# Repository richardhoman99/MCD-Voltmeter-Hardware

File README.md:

# MCD-Voltmeter-Hardware
The KiCad project for the MCD Voltmeter project.  
See "PCB Voltmeter Report.pdf"

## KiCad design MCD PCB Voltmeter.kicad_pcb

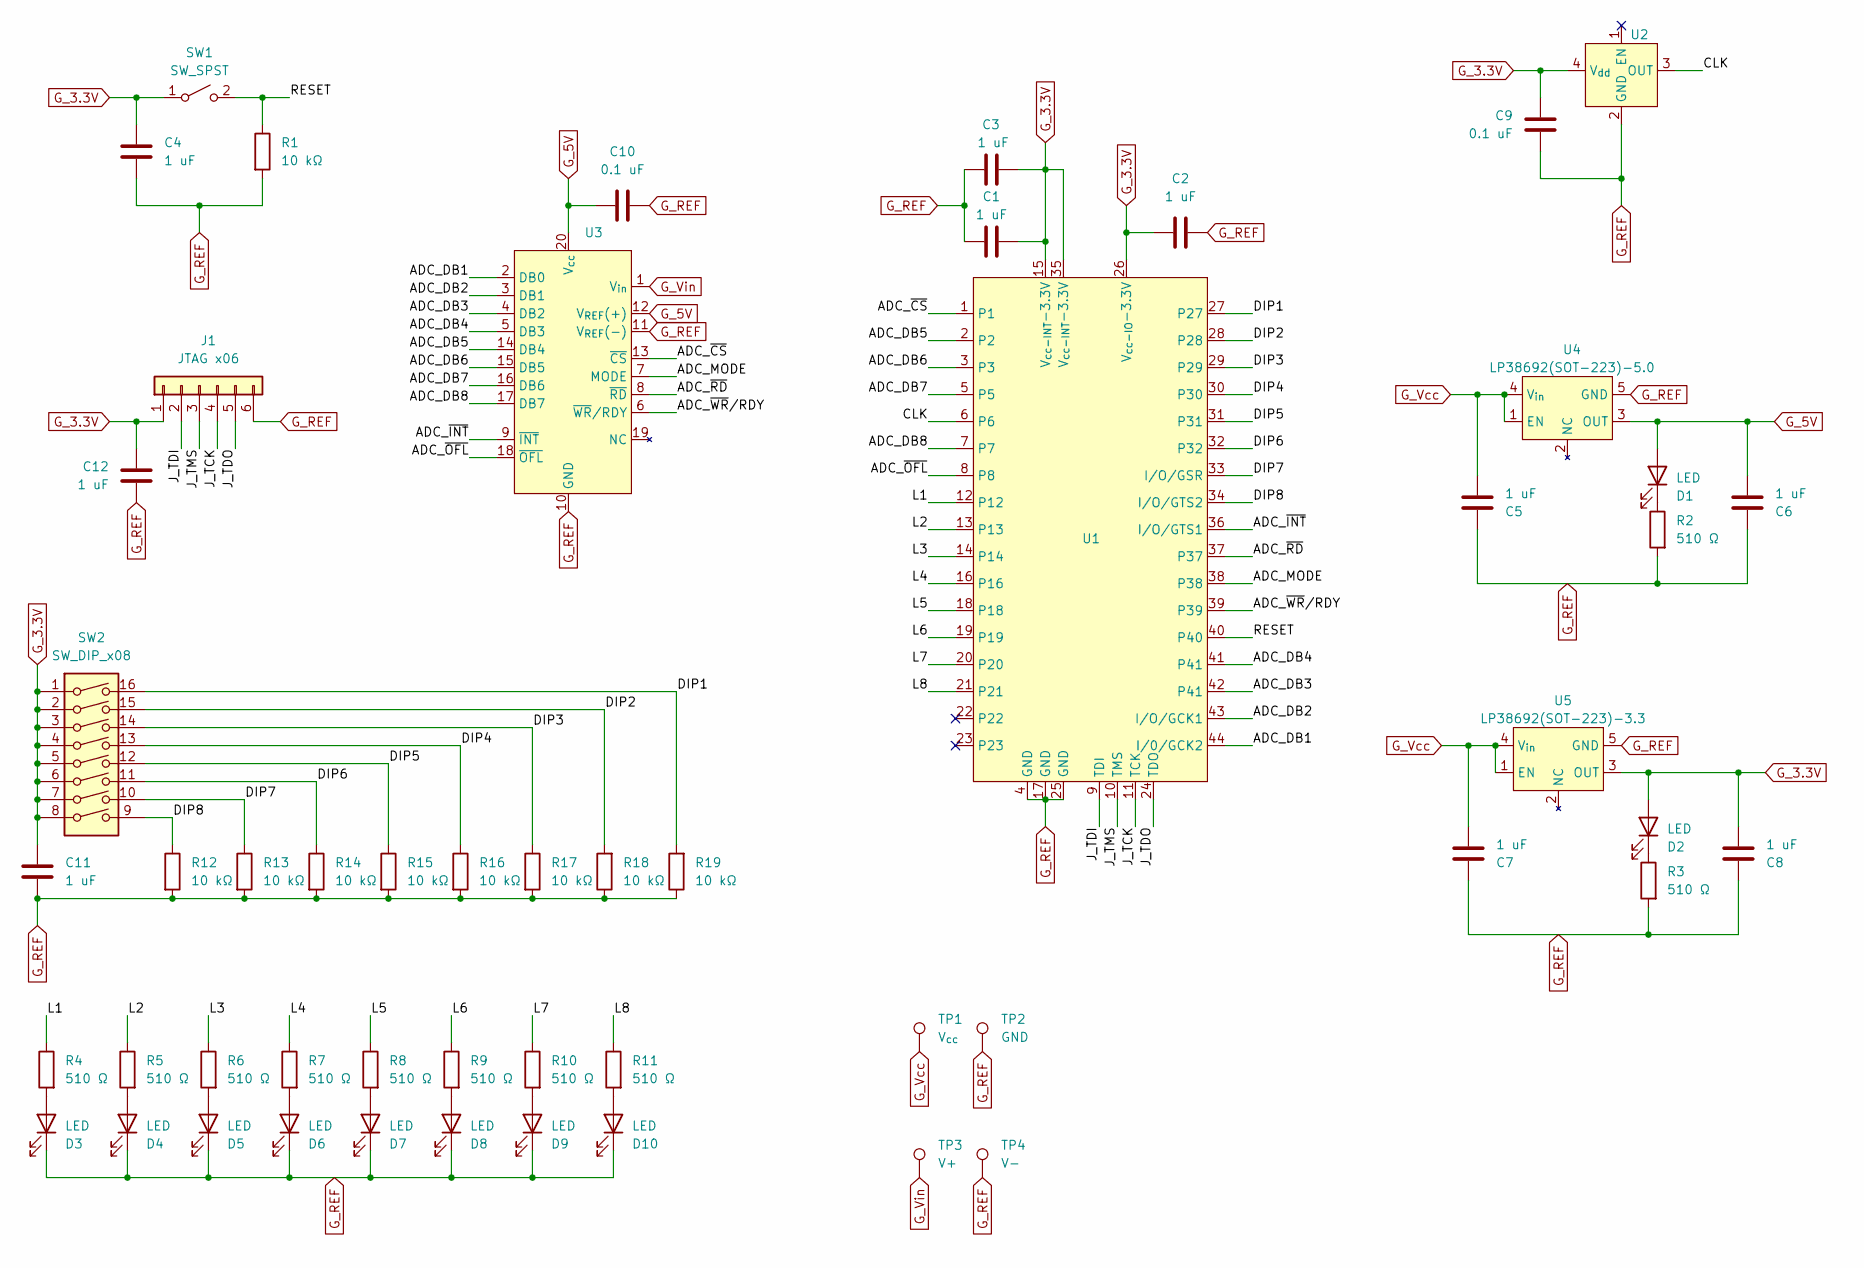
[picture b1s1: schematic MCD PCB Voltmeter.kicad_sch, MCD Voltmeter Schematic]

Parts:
C1, C2, C3, C4, C5, C6, C7, C8, C11, C12: 1 uF; C_0805_2012Metric
C9, C10: 0.1 uF; C_0805_2012Metric
D1, D2, D3, D4, D5, D6, D7, D8, D9, D10: LED; LED_0805_2012Metric
J1: JTAG x06; PinHeader_1x06_P2.54mm_Vertical
R1, R12, R13, R14, R15, R16, R17, R18, R19: 10 kΩ; C_0805_2012Metric
R2, R3, R4, R5, R6, R7, R8, R9, R10, R11: 510 Ω; C_0805_2012Metric
SW1: SW_SPST; SW_SPST_EVQQ2
SW2: SW_DIP_x08; SW_DIP_SPSTx08_Slide_6.7x21.88mm_W6.73mm_P2.54mm_LowProfile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
TP1: V_{cc}; TestPoint_Keystone_4952
TP2: GND; TestPoint_Keystone_4952
TP3: V+; TestPoint_Keystone_4952
TP4: V-; TestPoint_Keystone_4952
U1: VQFP-44_10x10mm_P0.8mm
U2: Crystal_SMD_5032-4Pin_5.0x3.2mm
U3: SOIC-20W_7.5x12.8mm_P1.27mm
U4: LP38692(SOT-223)-5.0; SOT-223-5
U5: LP38692(SOT-223)-3.3; SOT-223-5

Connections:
/ADC_DB1: U1.44 (I/0/GCK2), U3.2 (DB0)
/ADC_DB2: U1.43 (I/O/GCK1), U3.3 (DB1)
/ADC_DB3: U1.42 (P41), U3.4 (DB2)
/ADC_DB4: U1.41, U3.5 (DB3)
/ADC_DB5: U1.2, U3.14 (DB4)
/ADC_DB6: U1.3, U3.15 (DB5)
/ADC_DB7: U1.5, U3.16 (DB6)
/ADC_DB8: U1.7, U3.17 (DB7)
/ADC_MODE: U1.38, U3.7 (MODE)
/ADC_~CS: U1.1, U3.13 (~CS)
/ADC_~INT: U1.36 (I/O/GTS1), U3.9 (~INT)
/ADC_~OFL: U1.8, U3.18 (~OFL)
/ADC_~RD: U1.37, U3.8 (~RD)
/ADC_~WR/RDY: U1.39, U3.6 (~WR/RDY)
/CLK: U1.6, U2.3 (OUT)
/DIP1: R19.2, SW2.16, U1.27
/DIP2: R18.2, SW2.15, U1.28
/DIP3: R17.1, SW2.14, U1.29
/DIP4: R16.1, SW2.13, U1.30
/DIP5: R15.1, SW2.12, U1.31
/DIP6: R14.1, SW2.11, U1.32
/DIP7: R13.1, SW2.10, U1.33 (I/O/GSR)
/DIP8: R12.1, SW2.9, U1.34 (I/O/GTS2)
/J_TCK: J1.4, U1.11 (TCK)
/J_TDI: J1.2, U1.9 (TDI)
/J_TDO: J1.5, U1.24 (TDO)
/J_TMS: J1.3, U1.10 (TMS)
/L1: R4.1, U1.12
/L2: R5.1, U1.13
/L3: R6.1, U1.14
/L4: R7.1, U1.16
/L5: R8.1, U1.18
/L6: R9.1, U1.19
/L7: R10.1, U1.20
/L8: R11.1, U1.21
/RESET: R1.1, SW1.2 (B), U1.40
G_3.3V: C1.2, C2.1, C3.2, C4.1, C8.1, C9.1, C11.1, C12.1, D2.2 (A), J1.1, SW1.1 (A), SW2.1, SW2.2, SW2.3, SW2.4, SW2.5, SW2.6, SW2.7, SW2.8, U1.15 (V_{cc-INT}-3.3V), U1.26 (V_{cc-IO}-3.3V), U1.35 (V_{cc-INT}-3.3V), U2.4 (V_{dd}), U5.3 (OUT)
G_5V: C6.1, C10.1, D1.2 (A), U3.12 (V_{REF}(+)), U3.20 (V_{cc}), U4.3 (OUT)
G_REF: C1.1, C2.2, C3.1, C4.2, C5.2, C6.2, C7.2, C8.2, C9.2, C10.2, C11.2, C12.2, D3.1 (K), D4.1 (K), D5.1 (K), D6.1 (K), D7.1 (K), D8.1 (K), D9.1 (K), D10.1 (K), J1.6, R1.2, R2.2, R3.2, R12.2, R13.2, R14.2, R15.2, R16.2, R17.2, R18.1, R19.1, TP2.1, TP4.1, U1.4 (GND), U1.17 (GND), U1.25 (GND), U2.2 (GND), U3.10 (GND), U3.11 (V_{REF}(-)), U4.5 (GND), U5.5 (GND)
G_Vcc: C5.1, C7.1, TP1.1, U4.1 (EN), U4.4 (V_{in}), U5.1 (EN), U5.4 (V_{in})
G_Vin: TP3.1, U3.1 (V_{in})
unnamed: D1.1 (K), R2.1
unnamed: D2.1 (K), R3.1
unnamed: D3.2 (A), R4.2
unnamed: D4.2 (A), R5.2
unnamed: D5.2 (A), R6.2
unnamed: D6.2 (A), R7.2
unnamed: D7.2 (A), R8.2
unnamed: D8.2 (A), R9.2
unnamed: D9.2 (A), R10.2
unnamed: D10.2 (A), R11.2

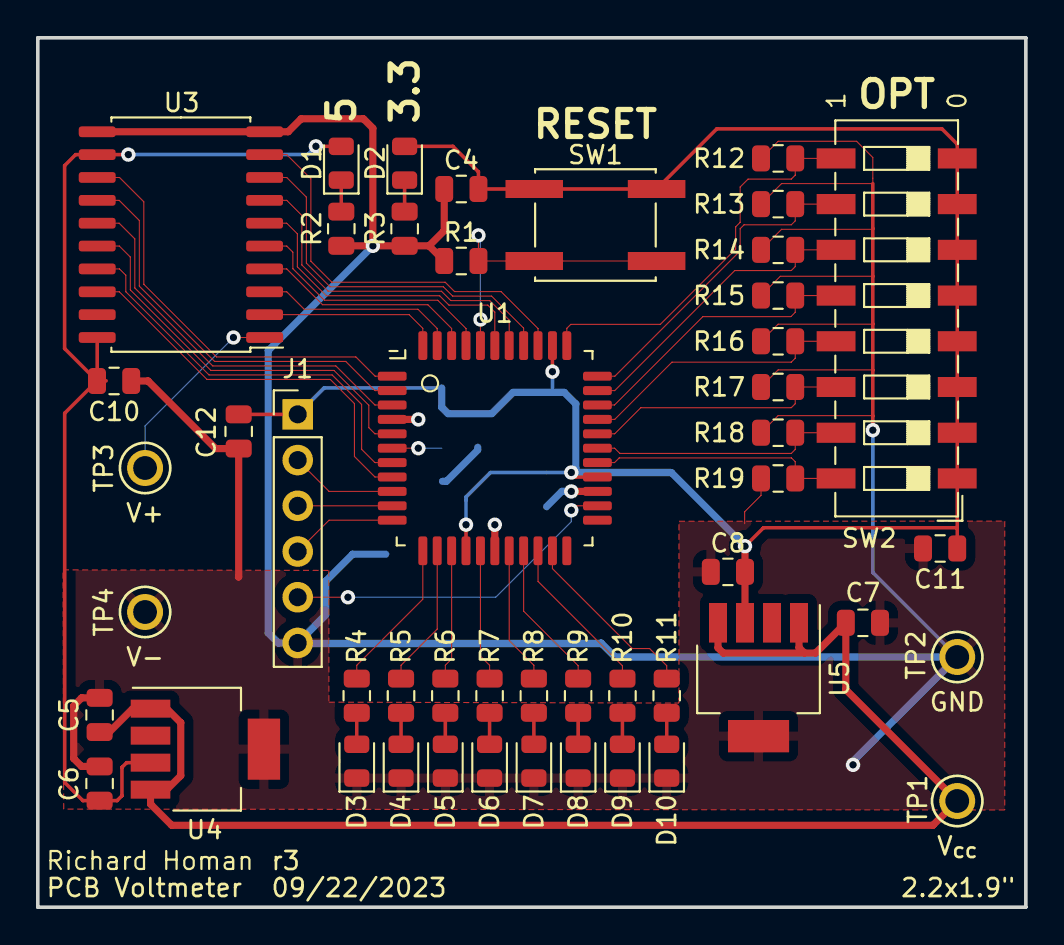
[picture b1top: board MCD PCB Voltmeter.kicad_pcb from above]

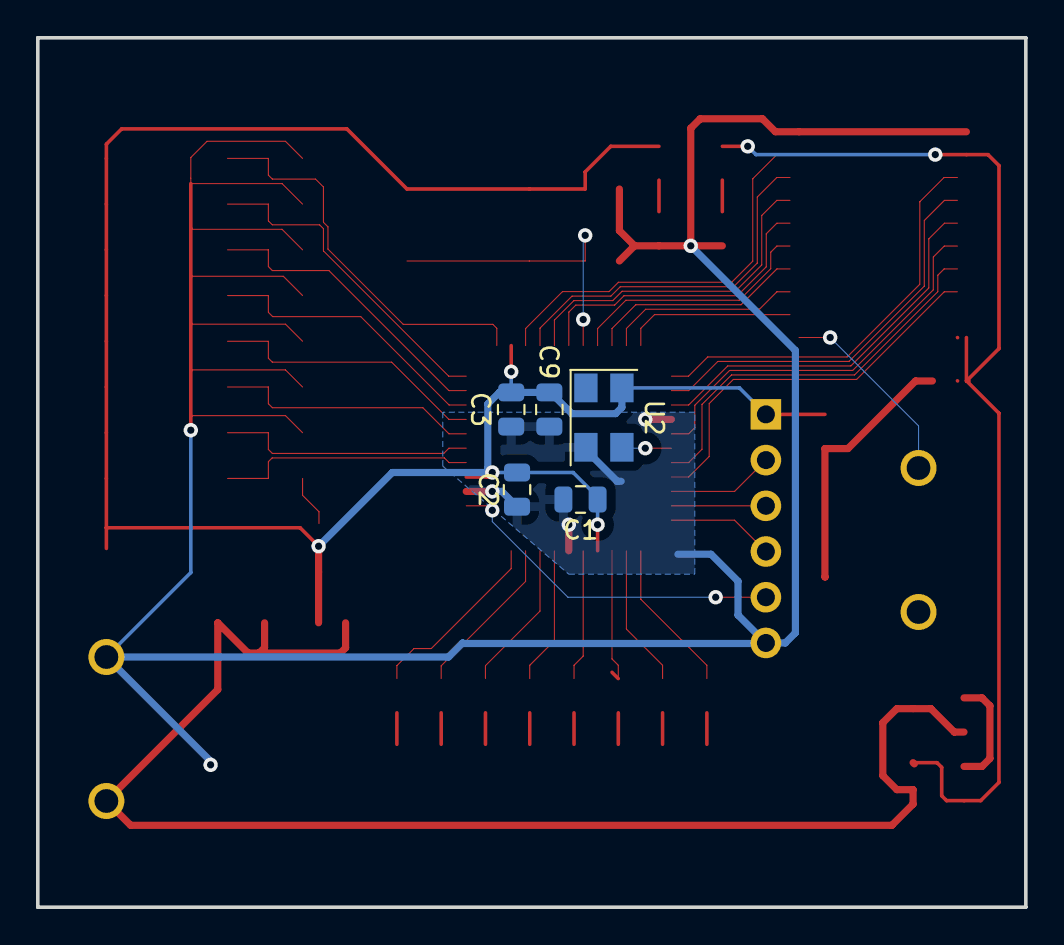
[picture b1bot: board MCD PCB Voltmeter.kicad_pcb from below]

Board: 2 copper layers, 54.9 x 48.3 mm, 53 parts (5 on the bottom side), 51 nets.

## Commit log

2023-11-03 Initial commit
    Copy items to Github
